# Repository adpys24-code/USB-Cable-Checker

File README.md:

<!-- boardrepo-badge:v1 -->

<!-- /boardrepo-badge:v1 -->

# USB Cable Checker

A passive continuity tester for USB cables, designed in KiCad 10.

Plug one end of a cable into a **source** connector and the other end into a
**sink** connector. Each conductor present in the cable lights its own LED, so
you can see at a glance whether a cable is charge-only, USB 2.0, or fully wired
for USB 3.x, and spot broken or missing wires.

Front view of PCB is in [`docs/board-top.png`](docs/board-top.png).

> [!WARNING]
> Never plug the checker into a real device, host or charger. Every contact on
> the source side, including GND and shield, sits at the test voltage.

## How it works

- **Source side (J1–J3):** every contact is tied to the test voltage, `VTEST`.
- **Sink side (J4–J9):** each contact position drives its own orange LED
  through a 1 kΩ resistor to GND (about 1 mA at 3 V). The sink connectors are
  wired in parallel, so a given LED always means the same contact, whichever
  sink connector you use.
- A conductor that runs through the cable completes the circuit and lights its
  LED. An unlit LED means that wire is missing or broken.

> [!WARNING]
> Never plug the checker into a real device, host or charger. Every contact on
> the source side, including GND and shield, sits at the test voltage.

The full schematic is in [`docs/usb-cable-checker-schematic.pdf`](docs/usb-cable-checker-schematic.pdf).

## Connectors

The sink connectors are labelled **a–f** on the silkscreen.

| Side | Ref | Board label | Connector |
|---|---|---|---|
| Source | J1 | TypeC 3.0 | USB-C (full 24-pin, USB 3.x) |
| Source | J2 | TypeA 2.0 | USB-A 2.0 |
| Source | J3 | TypeA 3.0 | USB-A 3.0 |
| Sink | J5 | a | USB-B 3.0 |
| Sink | J4 | b | USB-C (full 24-pin, USB 3.x) |
| Sink | J6 | c | Micro-B 3.0 |
| Sink | J7 | d | Mini-B |
| Sink | J8 | e | Lightning |
| Sink | J9 | f | Micro-B 2.0 |

## Reading the LEDs

The 26 LEDs follow the USB-C pin numbering and are labelled on the board in two
rows, **PINROW A** and **PINROW B**.

| LEDs | Contacts |
|---|---|
| D101–D112 | A1–A12: GND, TX1+, TX1−, VBUS, CC1, D+, D−, SBU1, VBUS, RX2−, RX2+, GND |
| D201–D212 | B1–B12: GND, TX2+, TX2−, VBUS, CC2, D+, D−, SBU2, VBUS, RX1−, RX1+, GND |
| D113 | ID (Mini-B / Micro-B) |
| D114 | Shield |

What to expect from a good cable:

| Cable | LEDs that light |
|---|---|
| Charge-only | VBUS and GND only |
| USB 2.0 (any connector type) | VBUS, GND, D+ and D− |
| USB 3.x (USB-A 3.0 to USB-B 3.0, Micro-B 3.0 or USB-C) | The USB 2.0 set, plus the TX and RX pairs |
| Full-featured USB-C to USB-C | VBUS, GND, D+/D−, one CC line, all four TX/RX pairs, SBU1 and SBU2 |

- A USB-C plug carries only one D+/D− pair and one CC line, so whether they
  show up in row A or row B depends on which way round the plug is. Flip it to
  check the other side.
- USB-A to USB-C cables contain a 56 kΩ resistor on CC, so the CC LED stays off
  or glows only faintly.
- The ID LED is normally off; most cables leave ID unconnected.
- The Shield LED lights only if the cable's shield runs from end to end.

Each row also has a round probe pad next to its label (TD1–TD26), so you can
measure a conductor with a multimeter.

## Power

SW1 selects the supply for `VTEST`:

- **CR2032 coin cell (BT1):** about 3 V, fed directly.
- **External 3–12 V on J10 (JST-PH 2-pin):** passes through the SS14
  reverse-polarity diode (D1) and the AMS1117-3.3 regulator (U1).

## Options and test pads

The solder jumpers are open by default.

| Ref | Function |
|---|---|
| JP1 | Bridge to tie sink CC1 to GND |
| JP2 | Bridge to tie sink CC2 to GND |
| JP3 | Bridge to tie sink shield to GND |
| TP1 / TP2 | Battery + / − pads beside the CR2032 holder |

## Board

| Top | Bottom |
|---|---|
|  |  |

- 85 × 70 mm, 2 layers, 1.6 mm thick, four M3 mounting holes
- 0603 LEDs and resistors. Every assembled part has an LCSC part number in
  `production/bom.csv`.

## Repository layout

| Path | Contents |
|---|---|
| `usb-cable-checker.kicad_pro` | KiCad project (open this) |
| `usb-cable-checker.kicad_sch` | Schematic |
| `usb-cable-checker.kicad_pcb` | PCB layout |
| `usb-cable-checker.kicad_dru` | Custom design rules |
| `fp-lib-table`, `sym-lib-table` | Project library tables (point into `lib/`) |
| `lib/usb_checker.kicad_sym` | Symbols for the connectors, battery holder and switch |
| `lib/usb_checker.pretty/` | Footprints for the connectors, battery holder, switch, test pads and LEDs |
| `lib/usb_checker.3dshapes/` | 3D models for the connectors, battery holder and switch |
| `production/gerbers/` | Gerber and drill files |
| `production/bom.csv` | Bill of materials (JLCPCB format, with LCSC part numbers) |
| `production/cpl.csv` | Component placement (pick-and-place) file |
| `docs/` | Schematic PDF and board renders |

The resistors, capacitors, LEDs, diode and regulator use KiCad's standard
libraries (`Device`, `Diode`, `Regulator_Linear`, `Resistor_SMD`,
`Capacitor_SMD`, `LED_SMD`, `Diode_SMD`, `Package_TO_SOT_SMD`), as do the
`power`, `Connector`, `Jumper` and `MountingHole` parts. Everything else is in
`lib/`, so the project opens on any standard KiCad 10 install.

## Ordering

1. Zip the contents of `production/gerbers/` and upload the zip to your PCB fab.
2. For JLCPCB assembly, also upload `production/bom.csv` and
   `production/cpl.csv`.

If you regenerate the placement file from KiCad, check the LED (D101–D212) and
regulator (U1) rotations in the fab's preview. The KiCad standard footprints for
these are rotated 180° from EasyEDA's, and the supplied `cpl.csv` already
accounts for that.

## License

Copyright 2026 USB Cable Checker contributors.

This source describes Open Hardware and is licensed under the CERN-OHL-P v2.
You may redistribute and modify this source and make products using it under
the terms of the CERN-OHL-P v2 (https://ohwr.org/cern_ohl_p_v2.txt). This
source is distributed WITHOUT ANY EXPRESS OR IMPLIED WARRANTY, INCLUDING OF
MERCHANTABILITY, SATISFACTORY QUALITY AND FITNESS FOR A PARTICULAR PURPOSE.
Please see the CERN-OHL-P v2 for applicable conditions. See [`LICENSE`](LICENSE).

### Third-party parts

The CERN-OHL-P covers the design. Some library parts in `lib/` were not created
for this project and keep their own terms:

- **Connector, battery-holder and switch parts** (the symbols, footprints and 3D
  models for J1–J10, BT1 and SW1) were converted from the
  [EasyEDA / LCSC](https://easyeda.com) component library with
  [easyeda2kicad](https://github.com/uPesy/easyeda2kicad.py). They are subject to
  EasyEDA's terms and are included only so the project opens complete.
- **`LED_0603_1608Metric_NoSilk`** is KiCad's `LED_SMD:LED_0603_1608Metric` with
  its silkscreen removed. It is licensed under
  [CC-BY-SA 4.0 with the KiCad library exception](https://www.kicad.org/libraries/license/).

The two test-pad footprints (`TestPad_Round_1.2mm`, `TestPad_Oval_3.0x5.0mm`)
were made for this project and are covered by the CERN-OHL-P.

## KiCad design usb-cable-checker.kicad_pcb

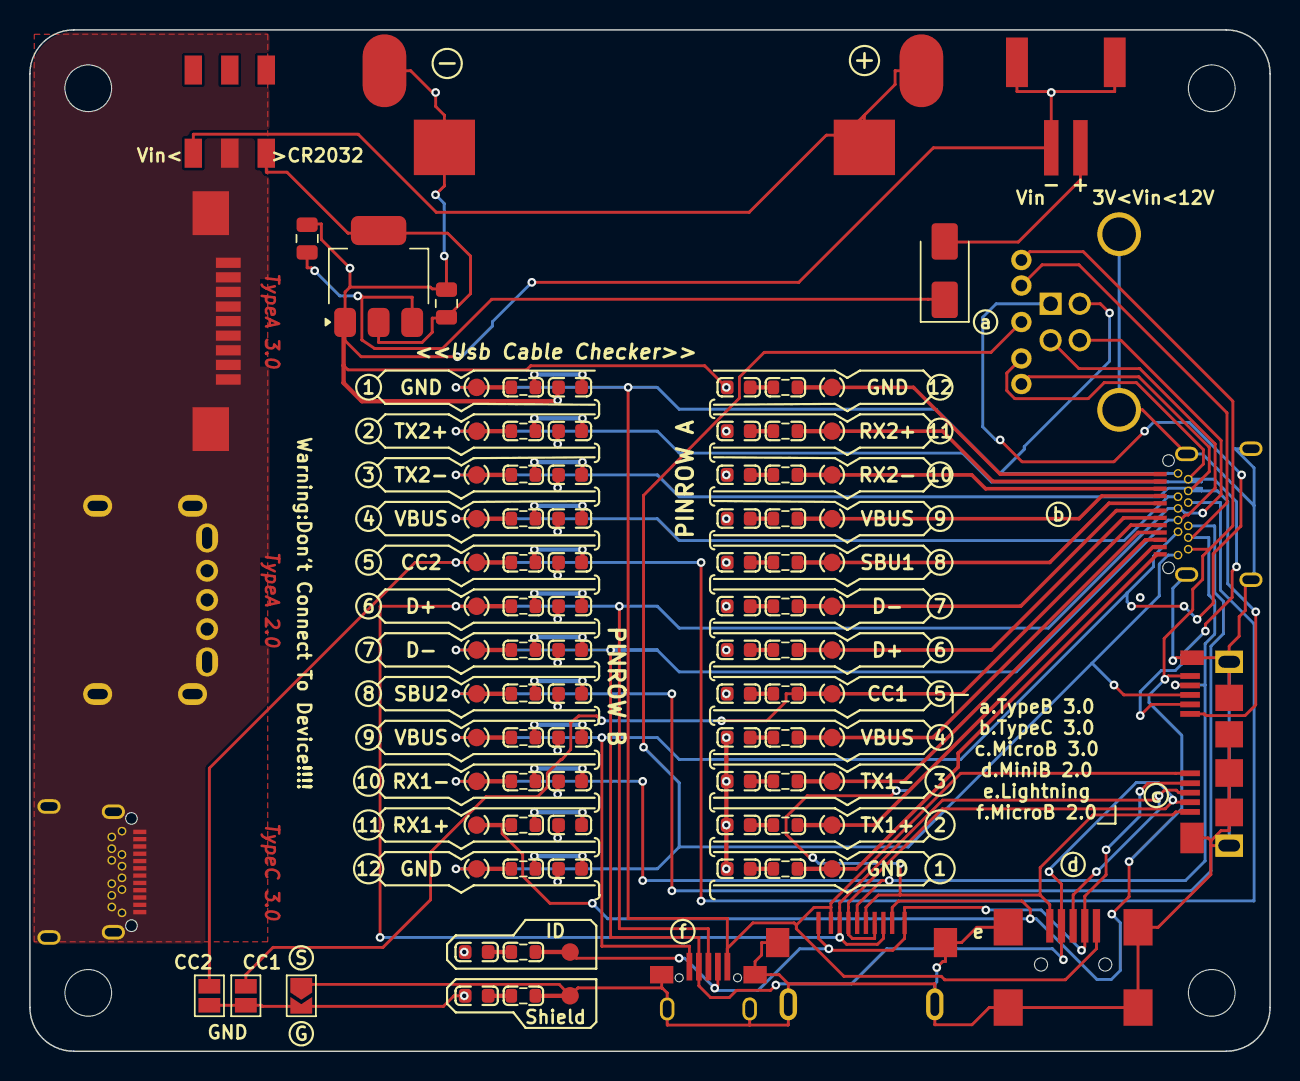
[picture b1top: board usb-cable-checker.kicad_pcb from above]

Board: 2 copper layers, 85.0 x 70.0 mm, 103 parts (0 on the bottom side), 58 nets.

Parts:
BT1: CR2032; BAT-TH_CR2032-BS-6-1
C1, C2: 10uF 25V; C_0805_2012Metric
D1: SS14; D_SMA
D101, D102, D103, D104, D105, D106, D107, D108, D109, D110, D111, D112, D113, D114, D201, D202, D203, D204, D205, D206, D207, D208, D209, D210, D211, D212: Orange; LED_0603_1608Metric_NoSilk
H1, H2, H3, H4: M3; MountingHole_3.2mm_M3
J1: USB-C 3.x (source); USB-C-SMD_TYPE-C-USB-20
J2: USB-A 2.0 (source); USB-A-TH_C168724
J3: USB-A 3.0 (source); USB-SMD_HC-USB3.0-L142-P
J4: USB-C 3.x (sink); USB-C-SMD_TYPE-C-USB-20
J5: USB-B 3.0 (sink); USB-B-TH_9P-L18.5-W12.0
J6: USB Micro-B 3.0 (sink); USB-SMD_ZX360D-B-10P-30
J7: USB Mini-B (sink); MINI-USB-SMD_U144-1245-161038
J8: Lightning (sink); USB-SMD-LIGHTNING_USB-PG
J9: USB Micro-B 2.0 (sink); MICRO-USB-SMD_MICRO-5.9ZB5.7-040
J10: VIN 3-12V; CONN-SMD_P2.00_S2B-PH-SM4-TB-LF-SN
JP1: CC1-GND; SolderJumper-2_P1.3mm_Open_Pad1.0x1.5mm
JP2: CC2-GND; SolderJumper-2_P1.3mm_Open_Pad1.0x1.5mm
JP3: S-G; SolderJumper-2_P1.3mm_Open_TrianglePad1.0x1.5mm
R101, R102, R103, R104, R105, R106, R107, R108, R109, R110, R111, R112, R113, R114, R201, R202, R203, R204, R205, R206, R207, R208, R209, R210, R211, R212: 1k; R_0603_1608Metric
SW1: Vin / CR2032; SW-SMD_MST22D18G2
TD1, TD2, TD3, TD4, TD5, TD6, TD7, TD8, TD9, TD10, TD11, TD12, TD13, TD14, TD15, TD16, TD17, TD18, TD19, TD20, TD21, TD22, TD23, TD24, TD25, TD26: TestPad_Round; TestPad_Round_1.2mm
TP1: BAT+; TestPad_Oval_3.0x5.0mm
TP2: BAT-; TestPad_Oval_3.0x5.0mm
U1: AMS1117-3.3; SOT-223-3_TabPin2

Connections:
/A1_GND: J4.A1, R101.1, TD2.1
/A2_TX1P: J4.A2, R102.1, TD4.1
/A3_TX1N: J4.A3, R103.1, TD6.1
/A4_VBUS: J4.A4, R104.1, TD8.1
/A5_CC1: J4.A5, JP1.1, R105.1, TD10.1
/A6_DP: J4.A6, R106.1, TD12.1
/A7_DN: J4.A7, R107.1, TD14.1
/A8_SBU1: J4.A8, R108.1, TD16.1
/A9_VBUS: J4.A9, R109.1, TD18.1
/A10_RX2N: J4.A10, R110.1, TD20.1
/A11_RX2P: J4.A11, R111.1, TD22.1
/A12_GND: J4.A12, R112.1, TD24.1
/B1_GND: J4.B1, J5.4, J6.5, J7.5, J8.2, J9.5, R201.1, TD1.1
/B2_TX2P: J4.B2, J5.6, J6.7, R202.1, TD3.1
/B3_TX2N: J4.B3, J5.5, J6.6, R203.1, TD5.1
/B4_VBUS: J4.B4, R204.1, TD7.1
/B5_CC2: J4.B5, JP2.1, R205.1, TD9.1
/B6_DP: J4.B6, J5.3, J6.3, J7.3, J8.3, J8.8, J9.3, R206.1, TD11.1
/B7_DN: J4.B7, J5.2, J6.2, J7.2, J8.4, J8.7, J9.2, R207.1, TD13.1
/B8_SBU2: J4.B8, R208.1, TD15.1
/B9_VBUS: J4.B9, J5.1, J6.1, J7.1, J8.6, J9.1, R209.1, TD17.1
/B10_RX1N: J4.B10, J5.8, J6.9, J8.5, R210.1, TD19.1
/B11_RX1P: J4.B11, J5.9, J6.10, J8.9, R211.1, TD21.1
/B12_GND: J4.B12, J5.7, J6.8, R212.1, TD23.1
/ID: J6.4, J7.4, J8.1, J8.10, J9.4, R113.1, TD25.1
/SHIELD: J4.0, J5.10, J5.11, J6.0, J7.6, J7.7, J7.8, J7.9, J8.11, J8.12, J8.13, J8.14, J9.6, J9.7, J9.8, J9.9, JP3.1, R114.1, TD26.1
/VBAT: BT1.1, SW1.3, TP1.1
/VIN_PROT: C1.1, D1.1, U1.3
/VIN_RAW: D1.2, J10.1
/VTEST: J1.0, J1.A1, J1.A2, J1.A3, J1.A4, J1.A5, J1.A6, J1.A7, J1.A8, J1.A9, J1.A10, J1.A11, J1.A12, J1.B1, J1.B2, J1.B3, J1.B4, J1.B5, J1.B6, J1.B7, J1.B8, J1.B9, J1.B10, J1.B11, J1.B12, J2.1, J2.2, J2.3, J2.4, J2.5, J2.6, J2.7, J2.8, J2.9, J3.1, J3.2, J3.3, J3.4, J3.5, J3.6, J3.7, J3.8, J3.9, J3.12, J3.13, SW1.2
/V_REG: C2.1, SW1.1, U1.2
GND: BT1.2, C1.2, C2.2, D101.1, D102.1, D103.1, D104.1, D105.1, D106.1, D107.1, D108.1, D109.1, D110.1, D111.1, D112.1, D113.1, D114.1, D201.1, D202.1, D203.1, D204.1, D205.1, D206.1, D207.1, D208.1, D209.1, D210.1, D211.1, D212.1, J10.2, J10.3, J10.4, JP1.2, JP2.2, JP3.2, TP2.1, U1.1
unnamed: D101.2, R101.2
unnamed: D102.2, R102.2
unnamed: D103.2, R103.2
unnamed: D104.2, R104.2
unnamed: D105.2, R105.2
unnamed: D106.2, R106.2
unnamed: D107.2, R107.2
unnamed: D108.2, R108.2
unnamed: D109.2, R109.2
unnamed: D110.2, R110.2
unnamed: D111.2, R111.2
unnamed: D112.2, R112.2
unnamed: D113.2, R113.2
unnamed: D114.2, R114.2
unnamed: D201.2, R201.2
unnamed: D202.2, R202.2
unnamed: D203.2, R203.2
unnamed: D204.2, R204.2
unnamed: D205.2, R205.2
unnamed: D206.2, R206.2
unnamed: D207.2, R207.2
unnamed: D208.2, R208.2
unnamed: D209.2, R209.2
unnamed: D210.2, R210.2
unnamed: D211.2, R211.2
unnamed: D212.2, R212.2

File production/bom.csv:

Comment,Designator,Footprint,LCSC,Quantity
CR2032,BT1,BAT-TH_CR2032-BS-6-1,C70377,1
10uF 25V,"C1,C2",C_0805_2012Metric,C15850,2
SS14,D1,D_SMA,C2480,1
Orange,"D101,D102,D103,D104,D105,D106,D107,D108,D109,D110,D111,D112,D113,D114,D201,D202,D203,D204,D205,D206,D207,D208,D209,D210,D211,D212",LED_0603_1608Metric_NoSilk,C965800,26
USB-C 3.x (source),J1,USB-C-SMD_TYPE-C-USB-20,C129018,1
USB-A 2.0 (source),J2,USB-A-TH_C168724,C168724,1
USB-A 3.0 (source),J3,USB-SMD_HC-USB3.0-L142-P,C7501876,1
USB-C 3.x (sink),J4,USB-C-SMD_TYPE-C-USB-20,C129018,1
USB-B 3.0 (sink),J5,USB-B-TH_9P-L18.5-W12.0,C7501849,1
USB Micro-B 3.0 (sink),J6,USB-SMD_ZX360D-B-10P-30,C598201,1
USB Mini-B (sink),J7,MINI-USB-SMD_U144-1245-161038,C53207143,1
Lightning (sink),J8,USB-SMD-LIGHTNING_USB-PG,C2858295,1
USB Micro-B 2.0 (sink),J9,MICRO-USB-SMD_MICRO-5.9ZB5.7-040,C2765188,1
VIN 3-12V,J10,CONN-SMD_P2.00_S2B-PH-SM4-TB-LF-SN,C295747,1
1k,"R101,R102,R103,R104,R105,R106,R107,R108,R109,R110,R111,R112,R113,R114,R201,R202,R203,R204,R205,R206,R207,R208,R209,R210,R211,R212",R_0603_1608Metric,C21190,26
Vin / CR2032,SW1,SW-SMD_MST22D18G2,C2906280,1
AMS1117-3.3,U1,SOT-223-3_TabPin2,C6186,1
